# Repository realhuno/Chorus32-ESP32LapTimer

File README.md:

# Chorus32-ESP32Laptimer

Some notes on using this fork:
 * Bluetooth is enabled by default, so you'll need to change the partition scheme to "HUGE APP" or something similar, so the sketch fits
 * Currently the initial power state of the modules is off, if the voltage reading is below 6V (this is to protect my already weak USB-Port during developement with multiple modules)
 * The module will always report 8 pilots. If the number of activated pilots is greater than the number of modules, multiplexing is enabled. If the number is lower the unsused modules are powered down. You can disable multiplexing for specific pilots on the settings page
 * EEPROM will be saved after a max of 10 sec
 * I'll regularly rebase and force push this branch ;)

This fork adds (mostly backend):
 * Mutliplexing modules. Reduces the accuracy, but is the only option if you want to go cheap and small
 * OLED page with lap times
 * Support for LoRa
 * Support for using a TCP connection. This should improve the connection quality (needs my fork of the app)
 * Some other changes I don't remember
 * Almost entirely usable without the app. Navigate to http://192.168.4.1/laptimes.html for in browser lap times. If your system supports text to speech the lap times will be spoken (for Linux speech-dispacher is responsible. You can test it with "spd-say 'hello world'")
 * Currently testing new peak detection method. See the wiki for some test results.
   * Compile with "DEBUG_SIGNAL_LOG" enabled, to print out (using USB) the last second of data after a lap has finished (this blocks the esp for a short while, so this is strictly used for data collection)
 * Much faster webinterface. Changing the settings is now much easier just enter a new value and be done. Green outline means the value is confirmed by the timer, orange means we are still waiting for a confirmation
    * You'll need to download  https://github.com/me-no-dev/ESPAsyncWebServer and https://github.com/me-no-dev/AsyncTCP as a .zip and add them in the Arduino IDE with "Sketch -> Include Library -> Add .ZIP Library..."

TODO:
 * Add race times to OSD (not sure how useful this will be, but I'll at least implement it)
 * Maybe support for checkpoints
 * Make useable without app
   * Continous mode
   * Statistics

This is an ESP32 port of the popular Chorus RF laptimer (https://github.com/voroshkov/Chorus-RF-Laptimer). Using an ESP32 provides much more processing power than AVR based Arduino boards and also has built in Wifi and Bluetooth networking simplifying connectivity options.

Compared to the original ChorusRF Lamptimer this ESP32 version only requires one RX module per pilot and a single ESP32 (nodemcu or similar) board. This allows you to connect your Lap timer wirelessly with no extra hardware required. However, due to ADC constraints, we are limited to 6 pilots per device. 

Hardware construction is also simplified as both parts are 3.3v logic and there is no need for level shifting or resistors.  

[Click HERE for a video showing the full setup process to get Chorus32 running on your ESP32 using Arduino IDE.](https://www.youtube.com/watch?v=ip2HUVk_lMs). 

[Click Here for German version Part 1](https://www.youtube.com/watch?v=z8xTfuLECME) [Part 2](https://www.youtube.com/watch?v=7wl0CgA8YnM).

Updates:
-----
*Important Notice for Chorus32 users!!!:*

As of last commit the default pinout has been changed to match that of the PCBs currently being tested.

For anyone that has built a Chorus32 with original schematics do not worry, your unit will continue working with future updates. However you must change `#define BOARD BOARD_DEFAULT` to `#define BOARD BOARD_OLD` in 'HardwareConfig.h' when compiling.

Added OLED and VBAT measurement support
Auto RSSI threshold setup is also not implemented, just set thresholds manually for now.

Added inital webserver configuration portal
https://www.youtube.com/watch?v=BVd2t0yO_5A/0.jpg

Application Support:
-----
Chorus32 communicates using the Chorus RF Laptimer API, which is supported by LiveTime.

LiveTime is an incredibly powerful and feature-rich timing system which runs on Windows. It is, however, quite complex, and likely overkill for most users. 

More information can be found here: https://www.livetimescoring.com/ 

If you are looking for a simpler setup, you can also use the Chorus RF Lap Timer app available for:

Android: https://play.google.com/store/apps/details?id=app.andrey_voroshkov.chorus_laptimer

iOS: https://itunes.apple.com/us/app/chorus-rf-laptimer/id1296647206?mt=8

Serial to UDP bridge. 
-----

To use this wirelessly with livetime you must use a third party application to a bridge vitural serial port with the UDP connection to the timer. The native ethernet TCP mode does not work at the moment. You can use this free application https://www.netburner.com/download/virtual-comm-port-driver-windows-xp-10/?fbclid=IwAR2W9V_YzjuP5_u9U-nJx1x38beFWNR0eRI59QOyYO_-NSePmTnW14kk7yA

Configure it like this:

Hardware:
-----
Construction is easy and only requires some basic point to point wiring of each module to the ESP32 board.

See HardwareConfig.h for pin assignments, it is possible to change any pin assignments apart from ADC channels. Note that pin assignments are GPIO hardware pin numbers and not pin numbers specific to the particular ESP32 development board you may be using. 

PCB designs are currently being tested

Performance:
-----
The Chorus32 Lap timer was compared to the $600USD ImmersionRC LapRF 8-Way at a local indoor event, arguably the worst conditions due to multipath and reflections. Results are presented below, you can see that the Chorus32 very closely matches the measured lap times of the LapRF.

## Compiling the Project:

#### Add esp32 to the Arduino IDE

Navigate to "File -> Preferences" and add "https://dl.espressif.com/dl/package_esp32_index.json" to "Additional Boards Manager URLs". If there is already an entry, just separate them with a ",".

Now navigate to "Tools -> Board -> Boards Manager..." search for "esp32" and click install.

#### Data Upload

To upload the files for the webpage you'll need to download https://github.com/me-no-dev/arduino-esp32fs-plugin/releases/ and extract it in "<Your Arduino install folder>/tools/". So that you end up with a folder called "ESP32FS" which has a folder "tool" inside of it.

#### Libraries

First head to "Sketch -> Include Library -> Manage Libraries" and search for "adafruit ina219" and "ssd1306 esp32" and install them both.
Now head to https://github.com/me-no-dev/ESPAsyncWebServer and https://github.com/me-no-dev/AsyncTCP and click on "Clone or download -> Download ZIP".
In the Arduino IDE nagivate to "Sketch -> Include Library -> Add .ZIP Library" and add them both.

#### Flashing
Now hit the upload button (with an arrow to the right) to upload the code to the board. After that upload the webpage data by clicking on "Tools -> ESP32 Sketch Data Upload". This should be done on every update!

You can edit file "HardwareConfig.h" to specify your board type and for some advanced configuration.

Now hit the upload button (with an arrow to the right) to upload the code to the board. After that upload the webpage data by clicking on "Tools -> ESP32 Sketch Data Upload". This should be done on every update!

##### For this branch you'll also need to change the default board in HardwareConfig.h to "BOARD_DEFAULT"

#### Updating

For updates either follow the normal flashing procedure or use the web UI.
To use the web UI updater open your Arduino IDE and click the verify button (the most left one).
Depending on your operating system there is a folder named "arduino_build_\<some numbers\>" in:
  - Linux: /tmp
  - Windows: %AppData%
  - OSX: No idea, sorry
  
Inside that folder should be a file called "ESP32LapTimer.ino.bin", which can be uploaded in the web interface.

Library requirements:
-----
Adafruit_INA219 https://github.com/adafruit/Adafruit_INA219

ESP8266 AND ESP32 OLED DRIVER FOR SSD1306 DISPLAY https://github.com/ThingPulse/esp8266-oled-ssd1306

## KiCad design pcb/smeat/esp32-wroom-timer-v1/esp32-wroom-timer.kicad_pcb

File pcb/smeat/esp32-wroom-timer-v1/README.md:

# Features
 - External edge mounted SMA connector for better range
   - Uses the esp32-wroom-32u
 - Integrated buck converter with correct components ;) (those modules from china are all over the place)
 - Footprint for an optional LoRa module
 - Space for 6 RX5808 modules
 - Optional ina219
    - I don't trust them anymore since one failed for me and put the input voltage on the 3.3V rail
 - Optional Fan with optional temperature sensor
 - Beeper

# Bugs
 - Wrong SMA footprint (still fits though)
 - Buzzer footprint is a little bit too small for my buzzers
 - A vertically mounted XT60 might be better

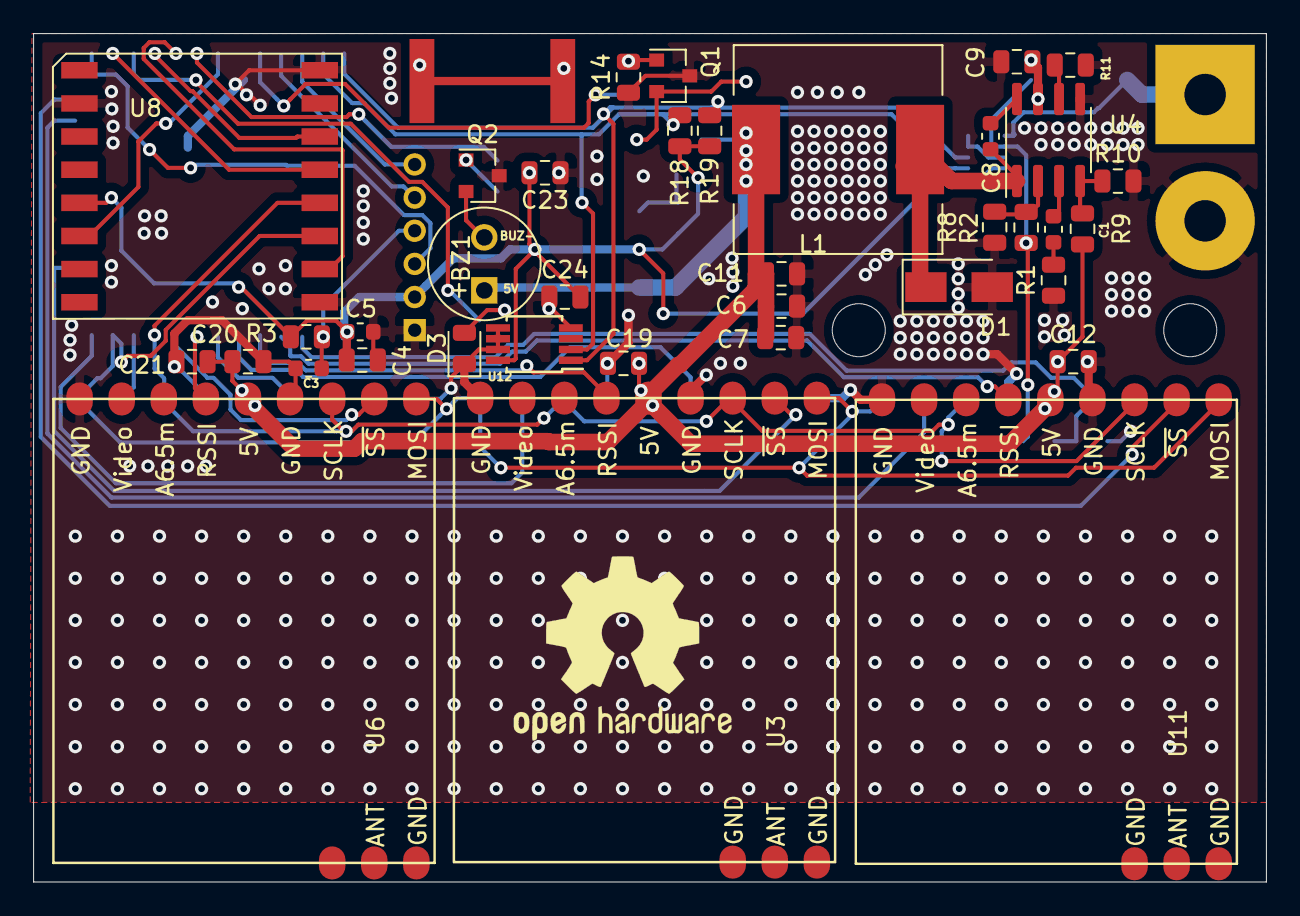
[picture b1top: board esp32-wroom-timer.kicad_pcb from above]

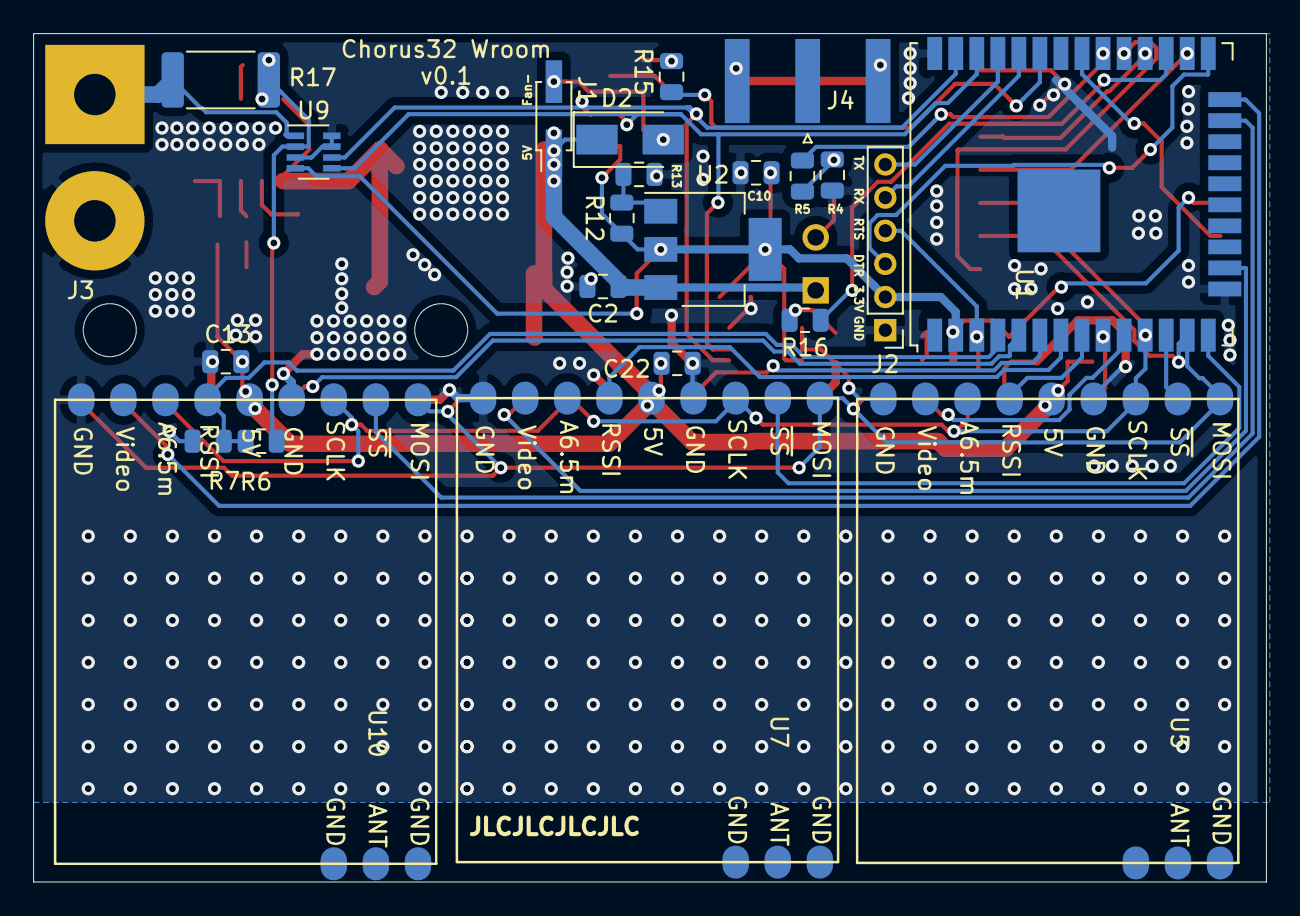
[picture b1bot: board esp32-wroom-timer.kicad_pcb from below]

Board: 2 copper layers, 74.4 x 51.2 mm, 63 parts (24 on the bottom side), 45 nets.

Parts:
BZ1: Buzzer; MagneticBuzzer_Kingstate_KCG0601
C1: 150pF; C_0603_1608Metric
C2, C4, C6, C7, C9, C10, C11, C12, C13, C19, C20, C21, C22, C23, C24: 10µF; C_0805_2012Metric
C3, C5, C8: 0.1µF; C_0603_1608Metric
D1: D_Schottky; D_SMA
D2: D; D_SMA
D3: LED; LED_0805_2012Metric
H1, H2: MountingHole; MountingHole_3.2mm_M3
J1: Fan_connector; PinHeader_2x01_P2.00mm_Vertical_SMD
J2: Programming; PinHeader_1x06_P2.00mm_Vertical
J3: input power; SolderWirePad_1x02_P7.62mm_Drill2.5mm
J4: Conn_Coaxial; SMA_Amphenol_132289_EdgeMount
L1: 22µH; L_12x12mm_H6mm
Q1, Q2: Q_NMOS_GSD; SOT-23
R1, R2, R11: 100k; R_0805_2012Metric
R3, R4, R7, R14, R18, R19: 10k; R_0805_2012Metric
R5, R15, R16: 1k; R_0805_2012Metric
R6: 240k; R_0805_2012Metric
R8: 59k; R_0805_2012Metric
R9: 210k; R_0805_2012Metric
R10: 40.2k; R_0805_2012Metric
R12: 240; R_0805_2012Metric
R13: 390; R_0805_2012Metric
R17: Shunt; R_2512_6332Metric
U1: ESP32-WROOM-32U
U2: AMS1117; SOT-223
U3, U5, U6, U7, U10, U11: RX5808; rx5808
U4: MP1584; SOIC-8_3.9x4.9mm_P1.27mm
U8: SX127_module; sx1276_module
U9: ina219; SOT-23-8
U12: MCP9804_MSOP; MSOP-8_3x3mm_P0.65mm

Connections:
+3V3: C4.2, C5.2, C10.1, C23.2, C24.2, J2.2, R3.1, R12.1, R18.1, R19.1, U1.2, U2.2, U2.4, U8.5, U9.4, U12.8
+5V: BZ1.1, C2.1, C6.2, C7.2, C11.2, C12.1, C13.1, C19.1, C20.1, C21.1, C22.1, D2.1, J1.1, L1.2, R9.2, U2.3, U3.5, U5.5, U6.5, U7.5, U10.5, U11.5
+28V: C9.1, R2.1, R6.2, R17.2, U4.7, U9.2
+BATT: J3.1, R17.1, U9.1
/ADC1: U1.9, U6.4
/ADC2: U1.8, U5.4
/ADC3: U1.6, U3.4
/ADC4: U1.7, U7.4
/ADC5: R6.1, R7.2, U1.4, U10.4
/ADC6: U1.5, U11.4
/BEEPER: R5.1, U1.30
/CLK: U1.11, U3.7, U5.7, U6.7, U7.7, U8.12, U10.7, U11.7
/CS1: U1.10, U6.8
/CS2: U1.12, U5.8
/CS3: U1.16, U3.8
/CS4: U1.14, U7.8
/CS5: U1.23, U10.8
/CS6: U1.24, U11.8
/DTR: J2.3, U1.25
/FAN_CONTROL: R15.1, U1.33
/LORA_CS: U1.26, U8.13
/LORA_IRQ: U1.31, U8.6
/LORA_RST: U1.28, U8.14
/MISO: U1.29, U8.10
/MOSI: U1.13, U3.9, U5.9, U6.9, U7.9, U8.11, U10.9, U11.9
/RTS: C3.1, J2.4, R3.2, U1.3
/RX0: J2.5, U1.34
/SCL: R18.2, U1.36, U9.5, U12.2
/SDA: R19.2, U1.37, U9.6, U12.1
/TX0: J2.6, U1.35
GND: C2.2, C3.2, C4.1, C5.1, C6.1, C7.1, C9.2, C10.2, C11.1, C12.2, C13.2, C19.2, C20.2, C21.2, C22.2, C23.1, C24.1, D1.2, D3.1, J2.1, J3.2, Q1.3, Q2.3, R1.1, R4.1, R7.1, R8.1, R10.2, R11.1, R13.1, R14.1, U1.1, U1.15, U1.38, U3.1, U3.6, U4.5, U5.1, U5.6, U6.1, U6.6, U7.1, U7.6, U8.2, U8.9, U8.16, U9.3, U9.7, U9.8, U10.1, U10.6, U11.1, U11.6, U12.4, U12.5, U12.6, U12.7
unnamed: BZ1.2, Q2.2
unnamed: C1.1, U4.3
unnamed: C1.2, R1.2
unnamed: C8.1, U4.8
unnamed: C8.2, D1.1, L1.1, U4.1
unnamed: D2.2, J1.2, Q1.2
unnamed: D3.2, R16.2
unnamed: Q1.1, R14.2, R15.2
unnamed: Q2.1, R4.2, R5.2
unnamed: R2.2, R8.2, U4.2
unnamed: R9.1, R10.1, U4.4
unnamed: R11.2, U4.6
unnamed: R12.2, R13.2, U2.1
unnamed: R16.1, U1.27

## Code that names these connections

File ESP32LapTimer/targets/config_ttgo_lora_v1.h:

#define BEEPER 4

#define LEDs 2

#define USE_CLASSIC_BUTTONS
  
#define BUTTON1 13
#define BUTTON2 12

#define MOSI 23
#define SCK 25

#define CS1 16
#define CS2 4 
#define CS3 4
#define CS4 4
#define CS5 4
#define CS6 4

#define ADC1 ADC1_CHANNEL_0
#define ADC2 ADC1_CHANNEL_3
#define ADC3 ADC1_CHANNEL_6
#define ADC4 ADC1_CHANNEL_5
#define ADC5 ADC1_CHANNEL_4
#define ADC6 ADC1_CHANNEL_7 // switched with adc 4 due to xtal

#define ADC1_GPIO 36
#define ADC2_GPIO 39
#define ADC3_GPIO 34
#define ADC4_GPIO 33
#define ADC5_GPIO 32
#define ADC6_GPIO 35

#define USE_LORA
#define LORA_SCK 5
#define LORA_MISO 19
#define LORA_MOSI 27
#define LORA_CS 18
#define LORA_RST 14
#define LORA_IRQ 26
#define LORA_FREQ 866E6

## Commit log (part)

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2019-12-24 Fix lap times page.
2019-12-24 [SCRIPT] Add support for dropping samples.
2019-12-24 Update readme.
2019-12-24 Add my PCB It takes an input voltage of 5V-26V, has space for 6 modules, an optional LoRa module, ina219, buzzer, fan pads, optional temperature sensor to control the fan. It uses an esp32 wroom 32u 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
2019-12-24 Fix bug when using the webpage to change pilot settings All pilots would get activated, regardless of settings.
2019-12-24 Small cleanup in ADC.
2019-12-24 [SCRIPT] Add script to analyze signal debug logs
2019-12-24 Add function to racetime.
2019-12-24 Fix threshold being float on website
2019-12-24 Allow any number as filter cutoff.
2019-12-24 Remove jquery dependency to make the SPIFFS < 190kb
2019-12-24 Add individual RSSI threshold to webpage.
2019-12-24 Use an async webserver
2019-12-24 Fix applying band and channel without multiplexing.
2019-12-24 Last minute PCB changes I hate those :/
2019-12-24 Fix calibration with multiplexing This stops adc reading and calibrates on core 0
2019-12-24 [SCRIPT] Add typing
2019-12-24 Fix selecting skip first lap in app.
2019-12-24 Add support for our extended commands.
2019-12-24 Make changes to my dev board I need to finish this pcb :/
2019-12-24 Some smaller fixes after rebase.
2019-12-24 Add option to configure eeprom commit interval.
    Lower eepromSave task.
    Minor cleanup.
2019-12-24 Add support for speaking the laptimes on the webpage and changing the pilot name.
2019-12-24 Disable min voltage by default
2019-12-24 Fix duplicate lap sending.
2019-12-24 Don't delete times when a race is stopped. They will be deleted, when a new lap starts.
2019-12-24 Trigger the lap on maximum rssi for all pilots. First tests have shown this yields an accuracy gain of about 60ms.
2019-12-24 Remove NUM_PHYSICAL_RECEIVERS and replace extern NumReceivers with a function. Closes #3.
2019-12-24 Add calibration progress to OLED
2019-12-24 [SCRIPT] Set input file for script as required
2019-12-24 Add race page with timings.
2019-12-24 Add support for logging multiple pilots
2019-12-24 Fix eeprom loading location. This fixes bringing up the module without multiplexing. By default pilots equal to the number of modules are active.
2019-12-24 [SCRIPT] Add support for comparing the data with a butterworth and bessel filter from scipy
2019-12-24 Add simple test to find out the module delay.
2019-12-24 Add dev target for me.
2019-12-24 Implement multiplexing
2019-12-24 Automatically disable all modules upon start when the voltage is too low. e.g. connecting via USB.
2019-12-24 Fix rebase
2019-12-24 [SCRIPT] Fix help in script
2019-12-24 [SCRIPT] Add support for multiple lowpass filters and specifying a separate sampling rate.
2019-12-24 Increase serial baud.
2019-12-24 Stop adc reading on core 0 when calibrating. Move calibration to core 0.
2019-12-24 Add output for websockets This will allow us to use the complete chorus API from the browser
2019-12-24 Add debug output and input switches
2019-12-24 Use a filter for voltage readings.
2019-12-24 Add debug mode to output the raw data after a lap. Will be used to examine how the peak looks like and test different peak detection methods.
2019-12-24 Add support for connectivity test
2019-12-24 Fix lap times.
2019-12-24 Only power the bare minimum for getting rssi.
    Make low power a compile time option.
    Low power increases the tune time and makes multiplexing worse.
2019-12-24 Add LapRelay program. Used as a relay for LoRa.
2019-12-24 Increase output buffer queue size.
2019-12-24 Add basic laptimes page.
2019-12-24 Highlight selected round
2019-12-24 Fix laptimes being 0.
2019-12-24 [SCRIPT] Make drawing the magnitude graph an argument
2019-12-24 Add support for changing the channel and band per pilot.
2019-12-24 Convert tabs to spaces.
2019-12-24 First working LoRa version. Still not very good and bad half-duplex and buffer handling.
2019-12-24 Add missing css file
2019-12-24 Add basic info about calibration. CSS is still TODO
2019-12-24 Honor skip first lap color pilot active status.
2019-12-24 Migrate the rest of the settings to websockets only calibration is missing but the redirect isn't that bad on this one.
2019-12-24 Function cleanup
2019-12-24 Add mangled/compressed javascript
2019-12-24 Update laptimes page to use websockets.
2019-12-24 Change upload speed to match the one from Arduino
2019-12-24 Remove old functions
2019-12-24 Ignore all inputs during update
2019-12-24 [WIP] Mouse controls to graph
2019-12-24 Fix pilot numbering on settings page.
2019-12-24 Add progress bar during update.
2019-12-24 Remove old laptimes file.
2019-12-24 Add build js script.
2019-12-24 Add more responsive settings for adc Others will follow.
2019-12-24 Send progress during update.
2019-12-24 Match the pilot colors with the app
2019-12-24 Make I2C pins configurable
2019-12-24 Fix vbat intendation on settings page
2019-12-24 Fix duplicate cmd.
2019-12-24 Use css for value status
2019-12-24 Fix reset button.
2019-12-24 Make the settings page more useable on a mobile device Probably still awful
2019-12-24 Add field for the number of laps.
2019-12-24 Add config file for my pcb
2019-12-24 Fix off by one error in queue.
2019-12-24 Add missing javascript file
2019-12-24 Move js files to a source folder.
2019-12-24 Add extended RSSI message Allows for better rssi logging
2019-12-24 Migrate display timeout
2019-12-24 Fix compilation with enabled buttons.
2019-12-24 [PCB] Add picture
2019-12-24 Add README for my new pcb
2019-12-24 Add script to generate constants for javascript.
2019-12-24 Add total time and place
2019-12-24 Use websockets for voltage.
2019-12-24 Move more styling to the css file Slowly learning ;)
2019-12-24 [WIP] make scrolling simpler
2019-12-24 Migrate wifi settings
2019-12-24 Highlight best lap A bunch of cleanup.
2019-12-24 [WIP] Add rssi graph to find potential missed laps
2019-12-24 Fix race counter
2019-12-24 Fix oled scrolling on summary page
2019-12-24 Webpage cleanup
2019-12-24 Fix voltage reading
2019-12-24 Use more template strings
2019-12-24 Refactor beeper code. Doesn't include any delays now.
2019-12-24 Fix invalid json with no active pilots.
2019-12-24 Migrate filter settings
2019-12-24 Allow upload of spiffs image
2019-12-24 Enable TCP by default
2019-12-24 [WIP] Fix aspect ratio and scrolling
2019-12-24 Migrate reset EEPROM
2019-12-24 Optimize sendExtendedCommandInt
2019-12-24 Check filename for "spiffs" during SPIFFS update
2019-12-24 [PCB] Fix resistor value
2019-12-24 Some fixes for the lappage
2019-12-24 Enable ArduinoOTA as a fallback update mechanism
2019-12-24 Add ability to enable and disable the pilot on the laptime page.
2019-12-24 Reliable load all available voices
2019-12-24 Enable RSSI history on laptimer page.
2019-12-24 Optimize addToSendQueue for larger data
2019-12-24 Set race mode on new laptime page.
2019-12-24 Fix incorrect variable name
2019-12-24 Fix voltage scaling
2019-12-24 Use css for best lap background
2019-12-24 Don't process websocket messages during updates
2019-12-24 Disable display support for my board
2019-12-24 Properly respond to setting the pilot active state
2019-12-24 Simplify code a little bit.
2019-12-24 Typo...
2019-12-24 Fix build_js
2019-12-24 Simplify platformio config and add custom partition scheme
2019-12-24 Set static limits for rssi chart.
2019-12-24 Update calibration values after calibrating without reloading
2019-12-29 Remove old functions Json is now replaced by websockets. Sending update status is not needed as the client can see the progress itself.
2019-12-29 First travis test.
2019-12-29 travis test.
2019-12-29 Fix LoRa boards
2019-12-29 partition fix
2019-12-29 test_releases
2019-12-29 Add gh token
2019-12-29 Add Travis CI and fix LoRa boards
2020-02-08 Add field to set the rssi graph update rate. I still have some problems with stuttering on my WROOM (does not happen on my dev module)
2020-02-08 Enable autoscoll again if scrolled to the end of the graph
2020-02-08 Treat mangled javascript as binary and update them.
2020-02-08 Disable pio ci and use "normal" compilation
2020-02-08 Add debug values to determine the memory allocation status
2020-02-16 Fix compilation with newest platformio Fixes #6.
2020-03-02 Add queue_init and queue_get
2020-03-02 Prevent overflow with too many laps Old laps are now phased out
2020-03-02 Make baud rate configurable and change it back to 115200
2020-03-02 Revert "Prevent overflow with too many laps"
    This reverts commit 2f0e90db10a660fb202e8f73e742baf088e25ff9.
    I don't really like memmove on the critical path. This might impact timing performance, and 100 laps should be enough. If you are in training you'll just have to restart eventually
2020-03-02 Don't send empty laps on invalid sendLap call
2020-03-02 Fix buffer overflow
2020-03-03 Add support for logging on all outputs
2020-03-06 [WIP] Add my wip telemetry code.
2020-03-06 [WIP] Add support for proxy commands in telemetry script.
2020-03-07 Update partition scheme (need to reflash using uartgit add -p .) eeprom is not used anymore.
2020-03-09 Add crash detection which will boot in OTA only mode on > 5 crashes.
2020-03-09 Fix i2c pins for default board
2020-03-09 Disable update firmware button until a file is selected
2020-03-09 Fix ci deploy
2020-03-09 Add missing files
2020-03-09 Remove old lines
2020-03-12 Add more "get" responses
2020-03-12 [WIP] Update telemetry script It is now able to change some chrous32 settings
2020-03-12 [WIP] Make OSD lap updates faster
2020-03-12 Add getter for filter value
2020-03-12 Add trigger mode message Instead of using experimental mode
2020-03-12 Add HEX_TO_UINT32 function
2020-03-12 [WIP] Add more settings to the lua script
2020-03-12 [WIP] Add racetime page for lua script
2020-03-13 [WIP] Add script support for pilot channels
2020-03-13 Add support for pilot active getter
2020-03-14 [DEBUG] Remove all serial noise
2020-03-14 Fix Terminator for bulk messages Thank you @realhuno
2020-03-14 Fix enumeration According to the documentation only the highest value is sent. Fixes compatability with racegod Thank you @realhuno
2020-03-14 OLED debug
2020-03-14 Fix OLED pins Not sure, what the problem was. Maybe a clash with the ina219? @realhuno finding all the bugs :D
2020-03-14 Undef oled if pins are not defined
2020-03-14 Fix build
2020-03-27 [UNTESTED] Remove pilot specific stuff out of RX5808. Use frequencies instead of band/channel for multiplexing.
2020-03-30 [SCRIPT] Add line to compare to old trigger method.
2020-03-30 Cleanup in webserver.
2020-03-30 Support multiple races on the web page.
2020-03-30 Go to prev page on long button1.
2020-03-30 Move skipfirstlap variable and check it when calculating the best lap.
2020-03-30 Multisample rssi during calibration and wait for rx to be ready.
2020-03-30 Only use new trigger mode when experimental is activated.
2020-03-30 Add compiler optimizations
2020-03-30 Add support for disabling multiplexing on a per pilot basis.
2020-03-30 Allow setting the client active and multiplex state from the web.
2020-03-30 Small html cleanup
2020-03-30 Add support for LoRa communication.
    Fix compilation without lora
2020-03-30 Disable all modules on brownout reboot.
2020-03-30 Fix brownout logic and reenable minimum voltage default Otherwise I am unable to use my module to develop.
2020-03-30 Show current race status and save last selected values
2020-03-30 Add CERN OHL for my PCB
2020-03-30 Add safety pullup resistors for i2c
2020-03-30 [LUA] Add threshold setting
2020-04-14 Compress all webserver files
2020-04-14 Add python script to prepare webpage data
2020-04-14 Add terser option. Too lazy to do all the rest
2020-04-15 Add data prepare script to pio and fix some issues
2020-04-15 Make compatible with python <3.8 Also delete the old data dir
2020-05-10 ADD OTA and RSSI
2020-05-24 RSSI an Webserver update
2020-05-29 Rapidfire Bridge added
2020-06-09 basic mqtt and rotorhazard support
2020-06-09 add mqtt ota
2020-06-20 mqtt autoconnect
2020-06-20 change to serial not serial1
2020-06-20 update LUA with laplist
2020-06-20 add laplist screen
